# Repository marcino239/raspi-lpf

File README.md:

# raspi-lpf
Low pass filter for WSPR on Raspberry Pi

Based on works by Paul Elliott March 2016
http://sjcars.org/blog/wp-content/uploads/2016/03/WSPR.pdf

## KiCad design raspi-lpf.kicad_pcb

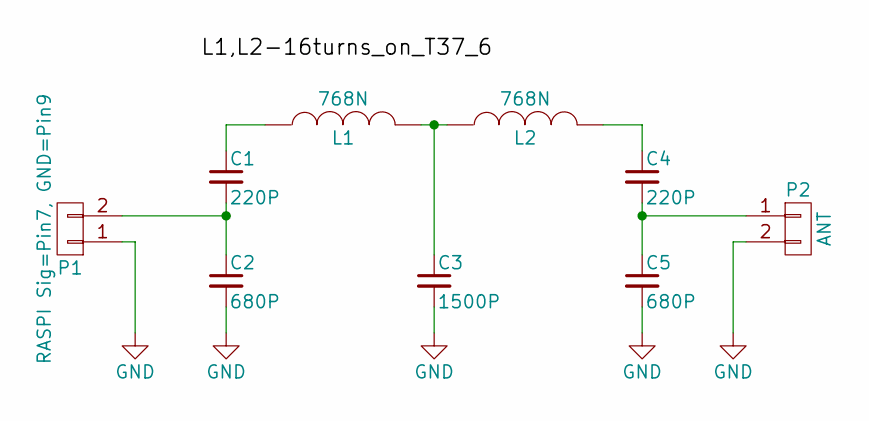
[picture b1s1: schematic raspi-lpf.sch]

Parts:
C1, C4: 220P; C_0805_HandSoldering
C2, C5: 680P; C_0805_HandSoldering
C3: 1500P; C_0805_HandSoldering
L1, L2: 768N; Choke_Toroid_6,5x13mm_Vertical
P1: RASPI Sig=Pin7, GND=Pin9; Pin_Header_Straight_1x02
P2: ANT; Pin_Header_Straight_1x02

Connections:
GND: C2.2, C3.2, C5.2, P1.1, P2.2
unnamed: C1.1, L1.1
unnamed: C1.2, C2.1, P1.2
unnamed: C3.1, L1.2, L2.1
unnamed: C4.1, L2.2
unnamed: C4.2, C5.1, P2.1

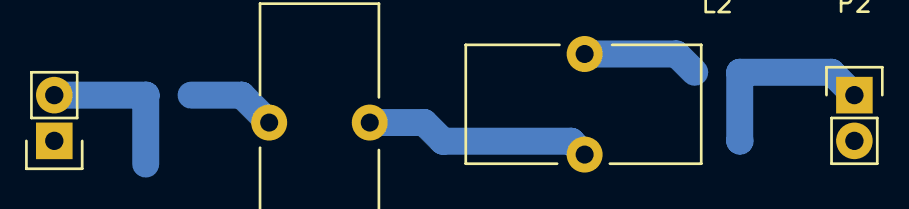
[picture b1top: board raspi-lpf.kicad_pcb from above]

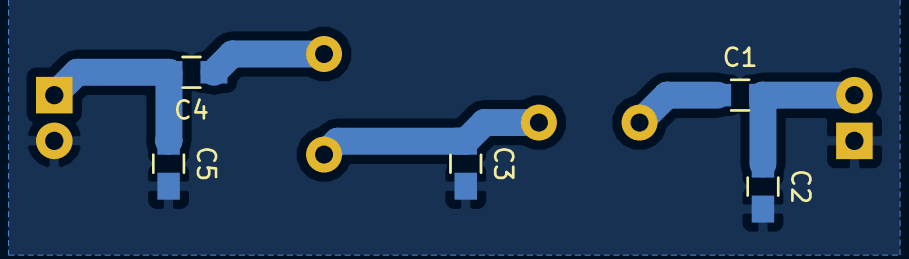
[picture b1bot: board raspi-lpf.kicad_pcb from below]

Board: 2 copper layers, 9 parts (5 on the bottom side), 6 nets.

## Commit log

2016-08-08 initial version
